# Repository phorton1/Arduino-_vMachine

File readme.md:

# The vMachine - Home

**Home** --
**[History](docs/history.md)** --
**[Hardware](docs/hardware.md)** --
**[Electronics](docs/electronics.md)** --
**[User Interface](docs/ui.md)** --
**[Software](docs/software.md)** --
**[Installation](docs/installation.md)**

The vMachine is a full featured proof-of-concept implementation of a **V plotter**.
It is essentially a CNC machine that uses *triangular kinematics* to work in a
cartesian coordinate system.

It is based on the inexpensive, yet powerful **ESP32** module, rather than the usual
Arduino class proessors.  The ESP32 can easily be programmed from within the
Arduino development environment and has *dual cores*, runs at *240 Mhz* (as opposed to
the Arduino at 16Mhz) and comes with *520KB* (as opposed to 2KB) *of RAM*.  In addition
the ESP32 includes full onboard **WiFi and Bluetooth** capabilities, and can be had for
$5, or about half the price of a genuine Arduino.

Therefore my *primary design decision* was to base this, and my future CNC projects
on an ESP32 processor.

**VIDEO - introduction to the vMachine**

The vMachine project is intended to accomplish several goals. Firstly, I wanted
to start developing and publishing open source CNC machines with the ESP32.
And so I built the machine and now present the designs and information
needed to build one.

The vMachine includes a full **Web Browser User Interface** so that it can be
controlled wirelessly from your phone or computer via **WiFi**.  It can also be controlled
via the **serial port** on the ESP32, via **Telnet** on port 23, or via **Bluetooth**
for usage with commonly available gcode sender programs.
Finally, it can also store gcode files on the optional **SD Card** and run jobs entirely
locally, right on the ESP32, via the optional **Touch Screen User Interface**, without
involving any other devices.

This repository includes all of the files and information needed to
build a copy of this machine.  It includes the needed to **3D print** the plastic
parts, as well as the underlying Fusion 360 designs if you need
or want to modify the 3D printed parts. It includes all of the **schematics**
and information needed to breadboard or otherwise create the electronic circuits,
as well as the KiCad files behind those, and the Flatcam and GCode files I used to
mill my own **circuit boards** for this version.

I have tried to provide a general roadmap for building a vMachine on these
pages.

A specific goal of this vMachine project is that it is generally scalable
to a larger machine, specifically one that can work with 4x8 feet sheets
of plywood, using a router to cut the plywood, as with the
[Maslow CNC](https://www.maslowcnc.com/).
Credits go to the Maslow team, as my vMachine source code actually
contains a port of the **Maslow triangular kinematics** to the ESP32.
I hope to build such a machine in the near future, and it should be
relatively straight-forward to scale this project up to a larger
machine of some sort.  The size of the machine is entirely parameterized
within the software and user interface.

But most importantly, this project establishes a **general approach** to
building ESP32 based CNC machines of various types, not only the vMachine
but also typical 3 and 4 axis CNC machines.  It is entirely based on the
next generation
[FluidNC](https://github.com/bdring/FluidNC)
project, a hugely important codebase that I have
forked and modified slightly so-as to better be able build projects
within the Arduino IDE development environment.

## Running the demo files

Included in this repository are a number of ready-to-go **gcode files**
that you can run on the vMachine.  It is beyond the scope of this project
to teach you how to use Inkscape, or Flatcam, or Fusion 360, or any other
available program to create gcode files to feed to the vMachine.

But, if you build the machine, and populate the SD card from this
repository, there are some gcode files you can use right away to
test it, verify it is working correctly, and even produce some nice
drawings.  You can view the contents of these gcode files to see what
kind of gcode the vMachine expects so that you can produce it with
any of the above programs, or by hand, as necessary.

**VIDEO - Running the Demo Files**

The video above demonstrates the touch screen UI, the browser
based Web/Wifi UI, and the serial terminal user interface by running the following
"programs" (gcode files) via one of the user interfaces:

- **homing** - first we "home" the machine
- **center.g** - moves the sled to the center of the page
- **ruler.g** - starts at the center and prints a simple ruler pattern
- **draw_boxes.g** - draws boxes on the board itself around the work area and 12x9" and 11x8.5" paper sizes
- **/test8.5x11/test8.5x11.ngc** - a sophisticated test that draws rulers, shapes, a compass and a sailboat
on 11x8.5" paper

When you get your vMachine working, the first thing you will print will probably be
the **ruler.g**, and you can do that by just manually moving the sled to the approximate
center of the work area, before you get **homing** working.   Once you can **home**
the machine, and you setup the G55 and G56 coordinate systems, you can run the
**draw_boxes.g** gcode to draw the work area, and 12x9 and 11x8.5 alignment boxes
directly on the board.  Then you can tape a piece of (US letter) paper in the
11x8.5 alignment box and print the **test8.5x11.ngc** reference test sheet on that.

## Documentation

The documentation starts with this page, and includes the following additional
pages:

- **[History](docs/history.md)** - my personal historical perspectives and
photos of early prototypes and previous versions of the vMachine.
- **[Hardware](docs/hardware.md)** - details the physical
construction of the vMachine, including the 3D printing and mechanical parts.
- **[Electronics](docs/electronics.md)** - the schematics and home made circuit
boards for the machine.
- **[User Interface](docs/ui.md)** - a synopsis of the behavior of the
vMachine and it's generalized **FluidNC_UI** user interface.
- **[Software](docs/software.md)** - an overview of the software architecture
of the vMachine and FluidNC.
- **[Installation](docs/Installation.md)** - instructions on building and installing
the vMachine firmware onto the ESP32 using the Arduino IDE environment.

It is recommended that you read all these pages BEFORE constructing a vMachine.
In my opinion if you are going to build a machine from these sources, or part of them,
you should **START** with the **[Installation](docs/Installation.md)**
page and the first thing you should do is *build the firmware and install it*
to a bare ESP32 dev module with just a USB cable.

As part of *that* process it is required that you verify and and utilize the browser
based WiFi UI to the module and upload some files to the file system on the ESP32,
so with just the bare ESP32 module you can verify that the firmware is installed,
test the Web UI, and make sure that it runs more or less correctly BEFORE investing
any time in 3D printing or creating breadboards or printed circuit boards.

In any case, all of these pages, and this source, is provided in the hopes that
you will find it useful and/or interesting.

## License

I'm gonna have to do something here.  Yech, I hate those headers in source files.

## Credits

- To the [Maslow CNC](https://www.maslowcnc.com/) team for the kinematics.

- To **bdring** and the [FluidNC Team](https://github.com/bdring/FluidNC) for the core of this project.

<br>
<hr>
<div style="text-align: right">
<a href='docs/history.md'>NEXT</a><i> - more about the vMachine ...</i>
</div>

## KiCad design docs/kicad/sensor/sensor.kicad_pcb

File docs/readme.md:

# The vMachine - Home

**Home** --
**[History](history.md)** --
**[Hardware](hardware.md)** --
**[Electronics](electronics.md)** --
**[Software](software.md)** --
**[Installation](installation.md)**

The vMachine is a full featured proof-of-concept implementation of a **V plotter**.
It is essentially a CNC machine that uses *triangular kinematics* to work in a
cartesian coordinate system.

It is based on the inexpensive, yet powerful **ESP32** module, rather than the usual
Arduino class processors.  The ESP32 can easily be programmed from within the
Arduino development environment and has *dual cores*, runs at *240 Mhz* (as opposed to
the Arduino at 16Mhz) and comes with *520KB* (as opposed to 2KB) *of RAM*.  In addition
the ESP32 includes full onboard **WiFi and Bluetooth** capabilities, and can be had for
$5, or about half the price of a genuine Arduino.

Therefore my *primary design decision* was to base this, and my future CNC projects,
on an ESP32 processor.

**TODO: VIDEO - introduction to the vMachine (good thumbnail for front image**

The vMachine project is intended to accomplish several goals. First, I wanted
to start developing and publishing open source CNC machines with the ESP32.
And so I built the machine and now present the designs and information
needed to build one.

The vMachine includes a full **Web Browser User Interface** so that it can be
controlled wirelessly from your phone or computer via **WiFi**.  It can also be controlled
via the **serial port** on the ESP32, via **Telnet** on port 23, or via **Bluetooth**
for usage with commonly available gcode sender programs.
Finally, it can also store gcode files on the optional **SD Card** and run jobs entirely
locally, right on the ESP32, via the optional
[**Touch Screen User Interface**](https://github.com/phorton1/Arduino-libraries-FluidNC_UI)
, without involving any other devices.

TODO: create animated gif specific to _vMachine

This repository includes all of the files and information needed to
build a copy of this machine.  It includes the files needed to **3D print** the plastic
parts, as well as the underlying Fusion 360 designs if you need
or want to modify the 3D printed parts. It includes all of the **schematics**
and information needed to breadboard or otherwise create the electronic circuits,
as well as the KiCad files behind those, and the Flatcam and GCode files I used to
mill my own **circuit boards** for this version.

I have tried to provide a general roadmap for building a vMachine on these
pages.

A specific goal of this vMachine project is that it is generally scalable
to a larger machine, specifically one that can work with 4x8 feet sheets
of plywood, using a router to cut the plywood, as with the
[Maslow CNC](https://www.maslowcnc.com/).
Credits go to the Maslow team, as this vMachine source code actually
contains a *port* of the **Maslow triangular kinematics** to the ESP32.
I hope to build such a machine in the near future, and it should be
relatively straight-forward to scale this project up to a larger
machine of some sort.  The size of the machine is entirely parameterized
within the software and user interface.

But most importantly, this project establishes a **general approach** to
building ESP32 based CNC machines of various types, not only the vMachine
but also typical 3 and 4 axis CNC machines or any other kind of machine
I might choose to build in the future.  It is entirely based on the
next generation
[FluidNC](https://github.com/bdring/FluidNC)
project, a hugely important codebase that I have
forked and modified slightly so-as to better be able build projects
within the Arduino IDE development environment.

<br>

## Running the demo files

Included in this repository are a number of ready-to-go **gcode files**
that you can run on the vMachine.  It is beyond the scope of this project
to teach you how to use Inkscape, or Flatcam, or Fusion 360, or any other
available program to create gcode files to feed to the vMachine. You
may use any of those, or any other program you wish, to create gcode
files for the vMachine.

But, if you build the machine, and populate the SD card from the **sdCard folder**
in this repository, there are some gcode files you can use right away to
test it, verify it is working correctly, and even produce some nice
drawings.  You can also view the contents of these gcode files to see what
kind of gcode the vMachine expects so that you can produce it with
any of the above programs, or by hand, as necessary.

**TODO: VIDEO - Running the vMachine Demo Files**

The video above demonstrates the touch screen UI, the browser
based Web/Wifi UI, and the serial terminal user interface by running the following
"programs" (gcode files) via one of the user interfaces:

- **homing** - first we "home" the machine
- **center.g** - moves the sled to the center of the page
- **ruler.g** - starts at the center and prints a simple ruler pattern
- **draw_boxes.g** - draws boxes on the board itself around the work area and 12x9" and 11x8.5" paper sizes
- **/test8.5x11/test8.5x11.ngc** - a sophisticated test that draws rulers, shapes, a compass and a sailboat
on 11x8.5" paper

When you build a vMachine, the first thing you will print will probably be
**ruler.g**, and you can do that by just manually moving the sled to the approximate
center of the work area, before you get **homing** working.   Once you can **home**
the machine, and you setup the G55 and G56 coordinate systems, you can run the
**draw_boxes.g** gcode to draw the work area, and 12x9 and 11x8.5 alignment boxes
directly on the board.  Then you can tape a piece of (US letter) paper in the
11x8.5 alignment box and print the full **test8.5x11.ngc** reference gcode on that.

TODO: Image of test gcode output

<br>

## Documentation

The documentation starts with this page, and includes the following additional
pages:

- **[History](history.md)** - my personal historical perspectives and
photos of early prototypes and previous versions of the vMachine.
- **[Hardware](hardware.md)** - details the physical
construction of the vMachine, including the 3D printing and mechanical parts.
- **[Electronics](electronics.md)** - the schematics and home made circuit
boards for the machine.
- **[Software](software.md)** - contains an overview of the
**software architecture** and details about how to **configure** the vMachine
- **[Installation](Installation.md)** - instructions on building and installing
the vMachine firmware onto the ESP32 using the Arduino IDE environment.

It is recommended that you read all these pages BEFORE constructing a vMachine.
If you are going to build a machine from these sources, or part of them,
you should **START** with the **[Installation](Installation.md)**
page and the first thing you should do is *build the firmware and install it*
to a bare ESP32 dev module with just a USB cable.

As part of *that* process it is required that you verify and utilize the browser
based WiFi UI to the module and upload some files to the file system on the ESP32,
so with just the bare ESP32 module you can verify that the firmware is installed,
test the Web UI, and make sure that it runs more or less correctly BEFORE investing
any time in 3D printing or creating breadboards or printed circuit boards.

In any case, all of these pages, and this source, is provided in the hopes that
you will find it useful and/or interesting.

<br>

## Please Also See

Please also see another CNC machine based on the same architecture,
my implementation of an ESP32 3 axis machine on an inexpensive
[**CNC 3018**](https://github.com/phorton1/Arduino-esp32_cnc3018)
from China [ebay](https://www.ebay.com/itm/392298131168).

These "machines"  are relatively small INO programs.  They are built on top of a
number of other libraries that provide the bulk of the functionality.

- [**FluidNC**](https://github.com/phorton1/Arduino-libraries-FluidNC) - the next generation **ESP32 GRBL** machine
- [**FluidNC_UI**](https://github.com/phorton1/Arduino-libraries-FluidNC_UI) - a *touch screen user interface* for FluidNC
- [**FluidNC_Extensions**](https://github.com/phorton1/Arduino-libraries-FluidNC_Extensions) - some extensions to FluidNC

The core of the machines, the GRBL (g-code) interpreter, is based on the
[**FluidNC**](https://github.com/phorton1/Arduino-libraries-FluidNC)
library.  The operational details of the machine, what g-codes
are supported, the basic serial command protocol, the wifi and webserver,
the machine configuration, and most functional aspects of the machine are
provided by this library.

On top of FluidNC I have built
[**FluidNC_UI**](https://github.com/phorton1/Arduino-libraries-FluidNC_UI),
the *touch screen user interface*, as a library that can optionally
used in ESP32 CNC projects.
Please see this library for a **description of the *User Interface***.

I have also added a
[**FluidNC_Extensions**](https://github.com/phorton1/Arduino-libraries-FluidNC_Extensions)
library that contains a number
of features that are used in this, and other machines based on this system.
This library contains methods and objects to abstract and extend the FluidNC
core.  Specific contents at this time include:

- some easy to use debug/info/error **output methods**
- methods to abstract the **state** of the FluidNC machine
- methods to abstract **control** of the FluidNC machine
- methods to supplement the FluidNC **configuration** system, and
- an implementation of **mesh bed levelling**

<br>

## Credits and License

This library is licensed under the
[GNU General Public License v3.0](https://github.com/phorton1/Arduino-_vMachine/tree/master/LICENSE.TXT)

**Credits**

- To the [Maslow CNC](https://www.maslowcnc.com/) team for the kinematics.
- To **bdring** and the **FluidNC Team**

<br>
<hr>
<div style="text-align: right">
<a href='history.md'>NEXT</a><i> - more about the vMachine ...</i>
</div>

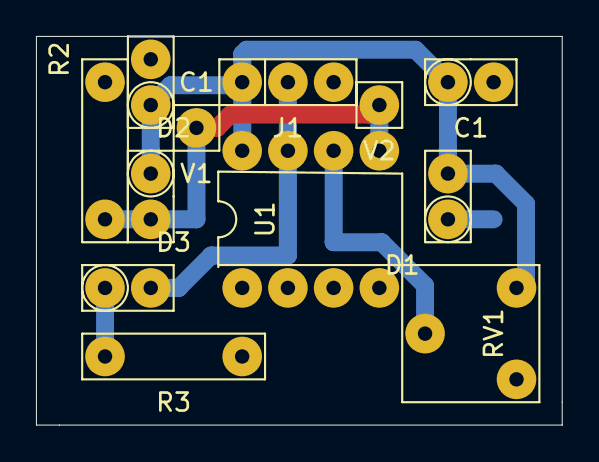
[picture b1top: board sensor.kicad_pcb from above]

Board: 2 copper layers, 29.2 x 21.6 mm, 12 parts (0 on the bottom side), 6 nets.

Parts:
C1, C1#2: 100nf; my2pin
D1: IR Emit; my2pin
D2: IR_Detect; my2pin
D3: LED; my2pin
J1: Conn_01x03; my3pin
R2: 10K; myResistor
R3: 220; myResistor
RV1: 10K; myTrimPot
U1: LM393; myDip8
V1, V2: Conn_01x01; my1pin

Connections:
unnamed: C1.1, C1#2.1, D1.2, D2.1, J1.1, RV1.1, U1.8
unnamed: C1.2, C1#2.2, J1.3, R2.1, R3.1, RV1.3, U1.4
unnamed: D2.2, R2.2, U1.5, V1.1, V2.1
unnamed: D3.1, R3.2
unnamed: D3.2, J1.2, U1.7
unnamed: RV1.2, U1.6

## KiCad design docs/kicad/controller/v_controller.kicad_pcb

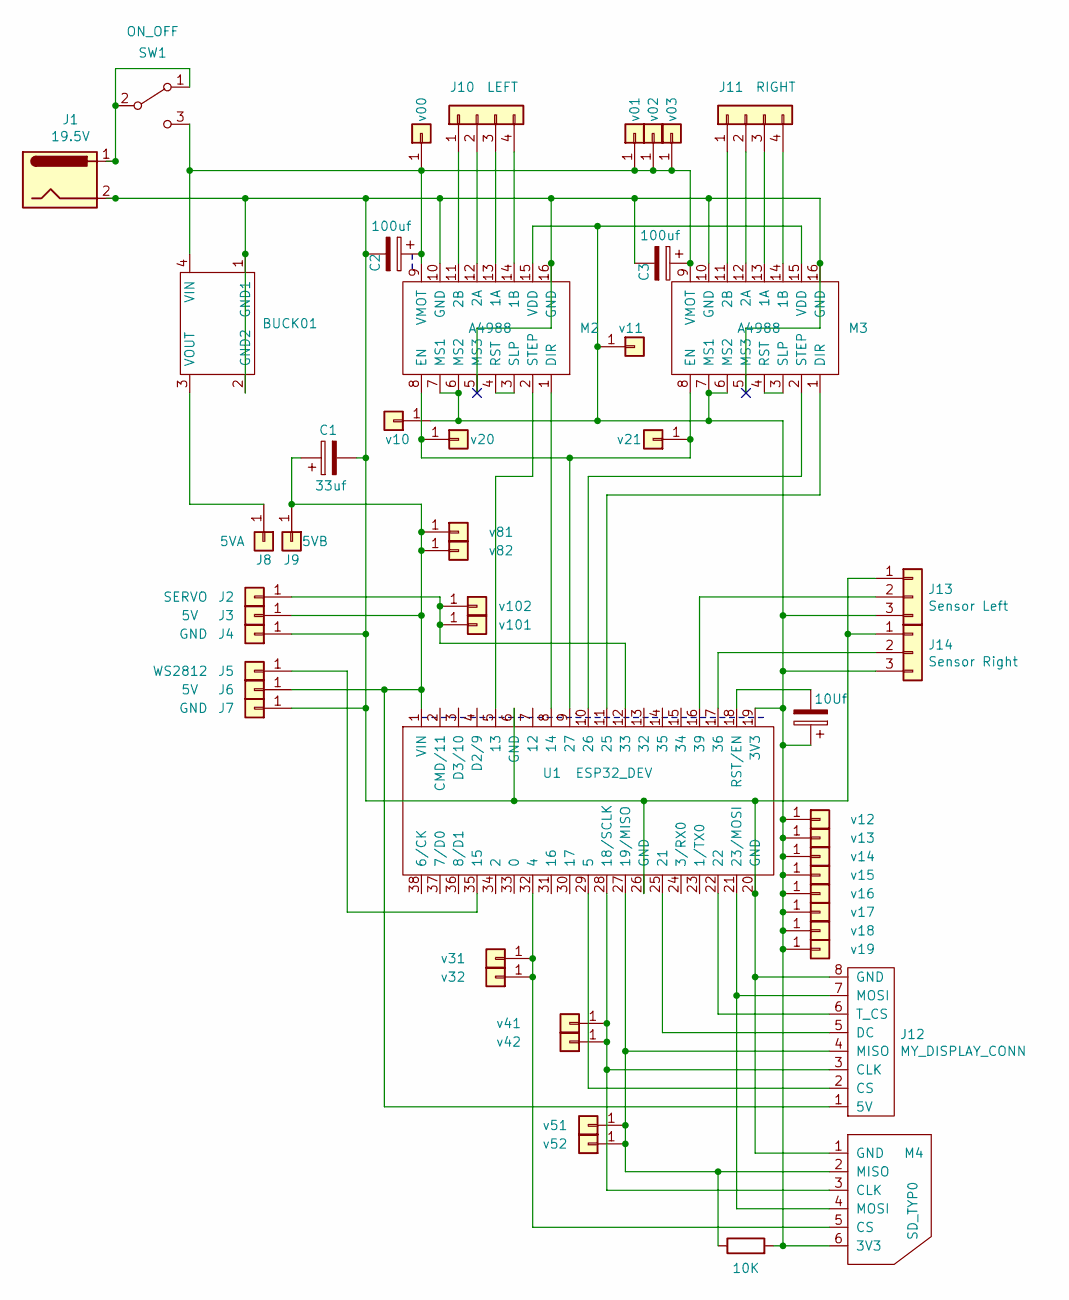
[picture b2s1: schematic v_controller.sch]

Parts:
C1: 33uf; my2pin
C2, C3: 100uf; my2pin
C4: 10Uf; my2pin
J1: 19.5V; myBarrelJack
J2: SERVO; my1pin
J3, J6: 5V; my1pin
J4, J7: GND; my1pin
J5: WS2812; my1pin
J8: 5VA; my1pin
J9: 5VB; my1pin
J10: LEFT; my4pin
J11: RIGHT; my4pin
J12: MY_DISPLAY_CONN; my8Pin
J13: Sensor Left; my3pin
J14: Sensor Right; my3pin
M1: BUCK01
M2, M3: A4988; a498
M4: SD_TYP0; my6Pin
R1: 10K; myResistor
SW1: ON_OFF; my3pin
U1: ESP32_DEV; ESP32-DEV
V1: v10; my1pin
V2: v00; my1pin
V3: v20; my1pin
V4: v01; my1pin
V5: v11; my1pin
V6: v12; my1pin
V7: v31; my1pin
V8: v21; my1pin
V9: v32; my1pin
V10: v41; my1pin
V11: v42; my1pin
V12: v51; my1pin
V13: v52; my1pin
V14: v13; my1pin
V15: v14; my1pin
V16: v15; my1pin
V17: v81; my1pin
V18: v82; my1pin
V19: v02; my1pin
V20: v03; my1pin
V21: v16; my1pin
V22: v17; my1pin
V23: v18; my1pin
V24: v19; my1pin
V25: v101; my1pin
V26: v102; my1pin

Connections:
unnamed: C1.1, J3.1, J6.1, J9.1, J12.1 (5V), U1.1 (VIN), V17.1, V18.1
unnamed: C1.2, C2.2, C3.2, J1.2, J4.1, J7.1, J12.8 (GND), J13.1, J14.1, M1.1 (GND1), M1.2 (GND2), M2.5 (MS3), M2.10 (GND), M2.16 (GND), M3.5 (MS3), M3.10 (GND), M3.16 (GND), M4.1 (GND), U1.6 (GND), U1.20 (GND), U1.26 (GND)
unnamed: C2.1, C3.1, M1.4 (VIN), M2.9 (VMOT), M3.9 (VMOT), SW1.3 (C), V2.1, V4.1, V19.1, V20.1
unnamed: C4.1, J13.3, J14.3, M2.6 (MS2), M2.7 (MS1), M2.15 (VDD), M3.6 (MS2), M3.7 (MS1), M3.15 (VDD), M4.6 (3V3), R1.2, U1.19 (3V3), V1.1, V5.1, V6.1, V14.1, V15.1, V16.1, V21.1, V22.1, V23.1, V24.1
unnamed: C4.2, U1.18 (RST/EN)
unnamed: J1.1, SW1.1 (A), SW1.2 (B)
unnamed: J2.1, U1.12 (33), V25.1, V26.1
unnamed: J5.1, U1.35 (15)
unnamed: J8.1, M1.3 (VOUT)
unnamed: J10.1, M2.11 (2B)
unnamed: J10.2, M2.12 (2A)
unnamed: J10.3, M2.13 (1A)
unnamed: J10.4, M2.14 (1B)
unnamed: J11.1, M3.11 (2B)
unnamed: J11.2, M3.12 (2A)
unnamed: J11.3, M3.13 (1A)
unnamed: J11.4, M3.14 (1B)
unnamed: J12.2 (CS), U1.29 (5)
unnamed: J12.3 (CLK), M4.3 (CLK), U1.28 (18/SCLK), V10.1, V11.1
unnamed: J12.4 (MISO), M4.2 (MISO), R1.1, U1.27 (19/MISO), V12.1, V13.1
unnamed: J12.5 (DC), U1.25 (21)
unnamed: J12.6 (T_CS), U1.22
unnamed: J12.7 (MOSI), M4.4 (MOSI), U1.21 (23/MOSI)
unnamed: J13.2, U1.16 (39)
unnamed: J14.2, U1.17 (36)
unnamed: M2.1 (DIR), U1.8 (14)
unnamed: M2.2 (STEP), U1.5 (13)
unnamed: M2.3 (SLP), M2.4 (RST)
unnamed: M2.8 (EN), M3.8 (EN), U1.9 (27), V3.1, V8.1
unnamed: M3.1 (DIR), U1.11 (25)
unnamed: M3.2 (STEP), U1.10 (26)
unnamed: M3.3 (SLP), M3.4 (RST)
unnamed: M4.5 (CS), U1.32 (4), V7.1, V9.1

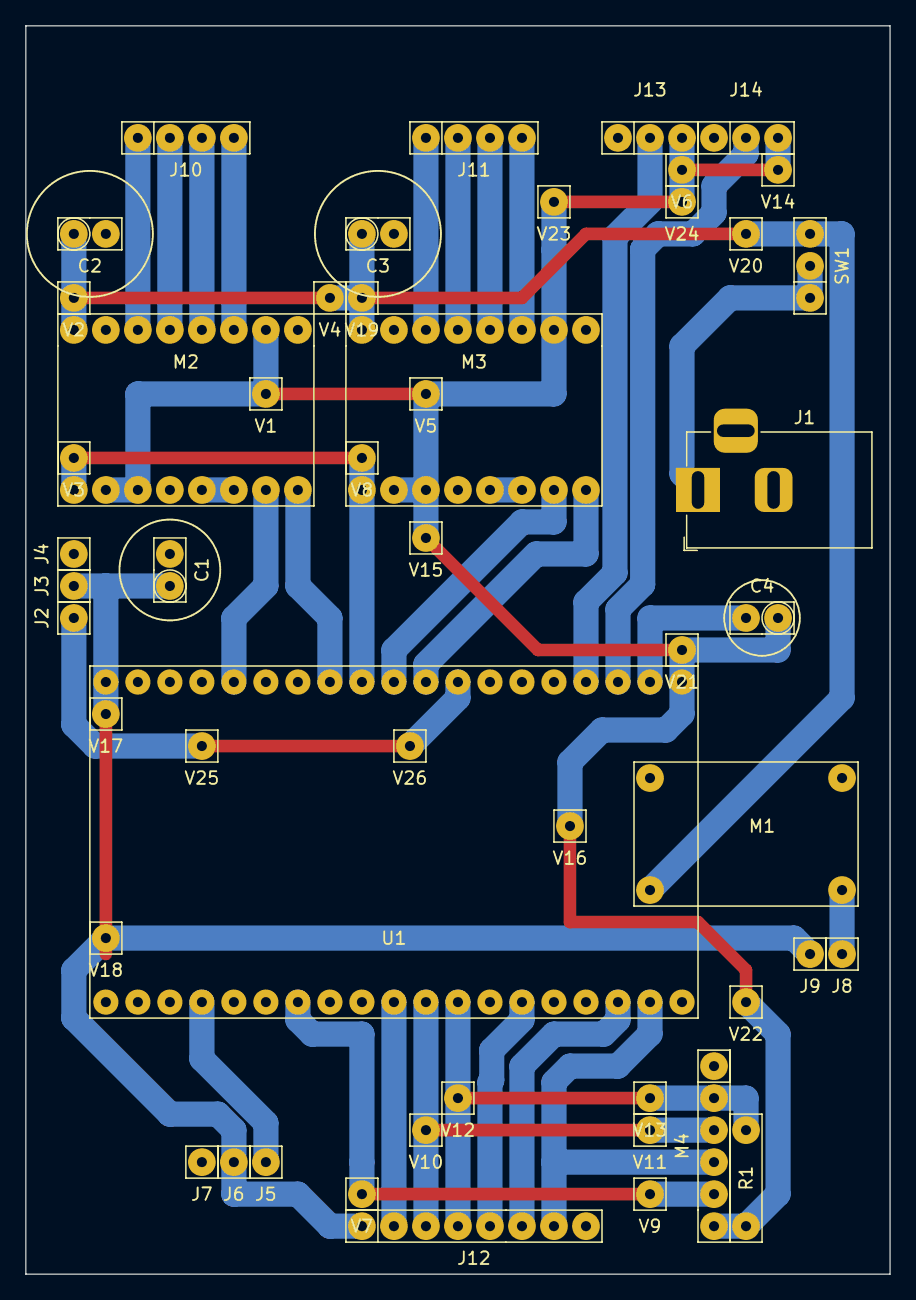
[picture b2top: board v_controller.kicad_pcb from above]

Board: 2 copper layers, 68.6 x 99.1 mm, 51 parts (0 on the bottom side), 33 nets.

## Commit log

2021-07-05 initial commit (after about 2 months of other gone repositories)
2021-07-09 remove nonsense due to bad idea to override core methods in Grbl_Esp32/PinMapper.cpp
2021-07-09 bring up ENABLE_TOUCH_UI with Monitor Text from Grbl_Esp32
2021-07-09 added .gitignore for preferences.txt
2021-07-10 keep SD Card open (don't call SD.end()) for initial touchUI testing
2021-07-10 Moved SD.begin() to vMachine.ino::aetup() and that FIXED the problematic SD.begin() problems Preparing to rework Grbl_Esp32 SDCard implementation to use protectedFS
2021-07-10 touched readme
2021-07-12 Cleanup (or not) - ino setup() mostly #ifdef'd out
2021-07-13 added memory diagnostics to debugging
2021-07-13 cleanup
2021-07-13 cleanup2
2021-07-14 slight change to vMemoryProbeTask()
2021-07-16 Allow vMachine to choose Grbl_MinUI library or Grbl_TouchUI library
2021-07-20 init sdCard the Grbl_Esp32 way for compatability ?!? (still inconsistent)
2021-07-21 changed WITH_APPLICATION and WITH_GRBL defines and include structure
2021-07-22 turn off annoying chain length message ...
2021-07-24 added V21812b LED Strip
2021-07-24 Sigh/lol - had it checked in with Line Segmentation commented out ..
2021-07-26 decouple from Grbl_Esp32 output routines; add memory footprint #defines
2021-07-26 fixed "bug" where motors were not disabled when idle that was due to yaml settings changing names and nesting levels
2021-07-28 turned off vMachine MEMORY_PROBE
2021-07-29 got rid of 3d printing files
2021-07-29 keep preferences.txt in github
2021-07-30 Configurtion Experiments
2021-08-05 re-added SD.begin() during ino setup() - seems to help
2021-08-05 remove memory debugging defines
2021-08-05 add delay to stop garbled asynch debug output
2021-08-05 accommodate API changes with most recent YamlSettings branch merge
2021-08-07 IMPLEMENT_YAML_OVERRIDES, add v_error(), cleanup, and come up on rebased fork changes
2021-08-07 a test file that shows "long endings" with Cycles after IDLE
2021-08-07 setDefaultPosition() on homing fail to get jog working after ^X CLEAR
2021-08-08 added SYSTEM LED
2021-08-26 use <YamlOverrides.h> from new Grbl_Extras library (untested)
2021-09-23 preliminary (untested) rebase to FluidNC
2021-09-23 rename Grbl_Esp32 to FluidNC
2021-09-24 rename v2812b.h to my_ws2812b.h - change "Grbl_Esp32" etc to "FluidNC" etc
2021-09-24 moved Mesh to FluidNC_extensions, standardized FluidDebug.h, and renamed UI test program
2021-09-27 bring _vMachine up to restructured FluidNC mas o menus
2021-10-07 update to new VMACH milled PC board
2021-10-11 removed www from vMachine sdCard and ruler.g from SPIFFS
2021-10-11 NEW VSENSORS - but no real code changes - added draw_boxes.g
2021-10-11 cleanup yaml and demo gcode files
2021-10-14 change g_debug() to g_info() for some things
2021-10-14 start using config.yaml (but keeping vMachine.yaml separate)
2021-10-14 initial commit of docs (WIP)
2021-10-14 added #ifdef WITH_PIXELS
2021-10-14 continuing documentation
2021-10-14 move readme.md to docs diretory
2021-10-14 creeated unlinked notes.md
2021-10-14 set machine specific SSID's in YAML
2021-10-15 documentation WIP
2021-10-16 documentation WIP - LICENSE.TXT
2021-10-16 documentation tree license & credits
2021-10-16 got rid of sofware.md readme files*
2021-10-16 update CNC3018_ESP and other denormalized kiCad stuff*
2021-10-16 added most vMachine TODO pics
2021-10-16 added youtube TODO's
2021-10-17 update to merge my fork with _main branch
2021-10-17 finish merge with _main branch of my fork of FluidNC project
2021-10-20 SCREEN_GRAB - implemented FluidNC_UI gApplication doScreenGrab and console.pm to write BMP files
2021-10-20 documentation - added some animated gifs, started UI docs
2021-10-21 documentation WIP - added ctrl-O 'pending screen grab' realtime command
2021-10-21 documentation WIP: TFT_eSPI and FluidNC_UI and screen grabs
2021-10-21 documentation: broken links and image filenames
2021-10-22 documentation
2021-10-23 spellcheck
2021-10-23 architecture documentation - renamed vMachine.cpp to vMain.cpp and vMachineSettings.cpp to vMachine.cpp
2021-10-23 cleanup vMachine.cpp - show configuration $ variables in software.md
2021-10-23 renamed CNC3028_ESP to esp32_cnc3018
2021-10-28 image filename case
2021-10-28 minor edits
2021-10-29 doc touches
2021-10-31 stepper notes
2021-10-31 change SDCard startup messages to INFO
2021-11-01 prepare for demo
2021-11-09 servoTest, esp32Camera, begin new bilgeAlarm architecture
2022-04-15 implement FluidNC_UI driver/size/rotation API - rename tft calibration data files
2023-01-12 got rid of (unused) local kicad cnc3018 library
2023-01-12 Revert "delete kicad cache files"
    This reverts commit 26811d4a772752f21859dc86b1342c1c486722f3.
2023-11-02 fix broken links across all repos with introduction of base-apps-gitUI::repoDocs.pm

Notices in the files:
docs/readme.md:
Credits and License:
This library is licensed under the
[GNU General Public License v3.0](https://github.com/phorton1/Arduino-_vMachine/tree/master/LICENSE.TXT)
Credits
